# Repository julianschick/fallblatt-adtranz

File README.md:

# Adtranz-Fallblattmodule

ESP32-Mikrocontrollercode und Leiterplattenlayouts für den Betrieb von 20 Adtranz-Fallblattmodulen mit Alphanumerischer Zeichenpalette.

## Funktionsweise

Wie in [diesem Mikrocontroller.net-Thread](https://www.mikrocontroller.net/topic/460531) auch gut mit Schaltplan erläutert, sind die Fallblattmodule mit einer absoluten Positionierung anhand einer 6-Bit-Gray-Codierungsscheibe versehen. 6 Infrarotdioden sind hinter einer auf der Hauptachse mitrotierenden Scheibe angebracht, deren ringförmige Aussparungen einen Gray-Code ergeben, der mit Infrarotsensoren auf der anderen Seite der Scheibe ausgelesen werden kann.

Meine Ansteuerung besteht aus einem Zentralmodul und einem Steckermodul für jedes einzelne Fallblattmodul. Das Steckermodul bzw. dessen Platine wird mit einen "Card-Edge-Connector" direkt an das Fallblattmodul angesteckt. Auf dem Steckermodul befindet sich lediglich ein Shift-Register und ein Komparatorchip. Der Motor wird, solange mit Betriebsspannung versorgt, solange weiterdrehen, bis der im Shift-Register eingestellte Code auf der Codierungsscheibe erreicht ist.

Auf dem Zentralmodul sitzt ein ESP32, der die als Daisy-Chain verbundenen Steckermodule bzw. deren Shift-Register als ein langes Shift-Register befüllt. Da die Steuerleitungen dieser Shift-Registerkette durchaus lang sind (ca. 2m) ist es erforderlich diese direkt am Ausgang 
des Mikrocontrollers seriell zu terminieren, da die saubere Signalübertragung durch Spiegelungseffekte andernfalls nicht mehr gewährleistet ist.

<div align="center">

</div>

Außerdem war [weitere Stabilisierung nötig](https://www.mikrocontroller.net/topic/573166) bei den Schaltvorgängen des Motor-Relais im Fallblattmoduls. Direkt an den Motor wurde ein 100nF-Entstörkondensator 'angefrankensteint'. Außerdem ist ein 10 Ohm/2,2uF Snubberglied über den Relaiskontakt (zwischen 24 VAC N auf der Steckermodulplatine und 'b' auf der Platine des Fallblattmoduls gelegt) um für Ruhe beim Schalten zu sorgen. Ohne diese Maßnahmen hat die Abschaltung des Motors bei erreichen der gewünschten Stellung der Hauptachse nicht gut funktioniert.

## Leiterplattenlayouts

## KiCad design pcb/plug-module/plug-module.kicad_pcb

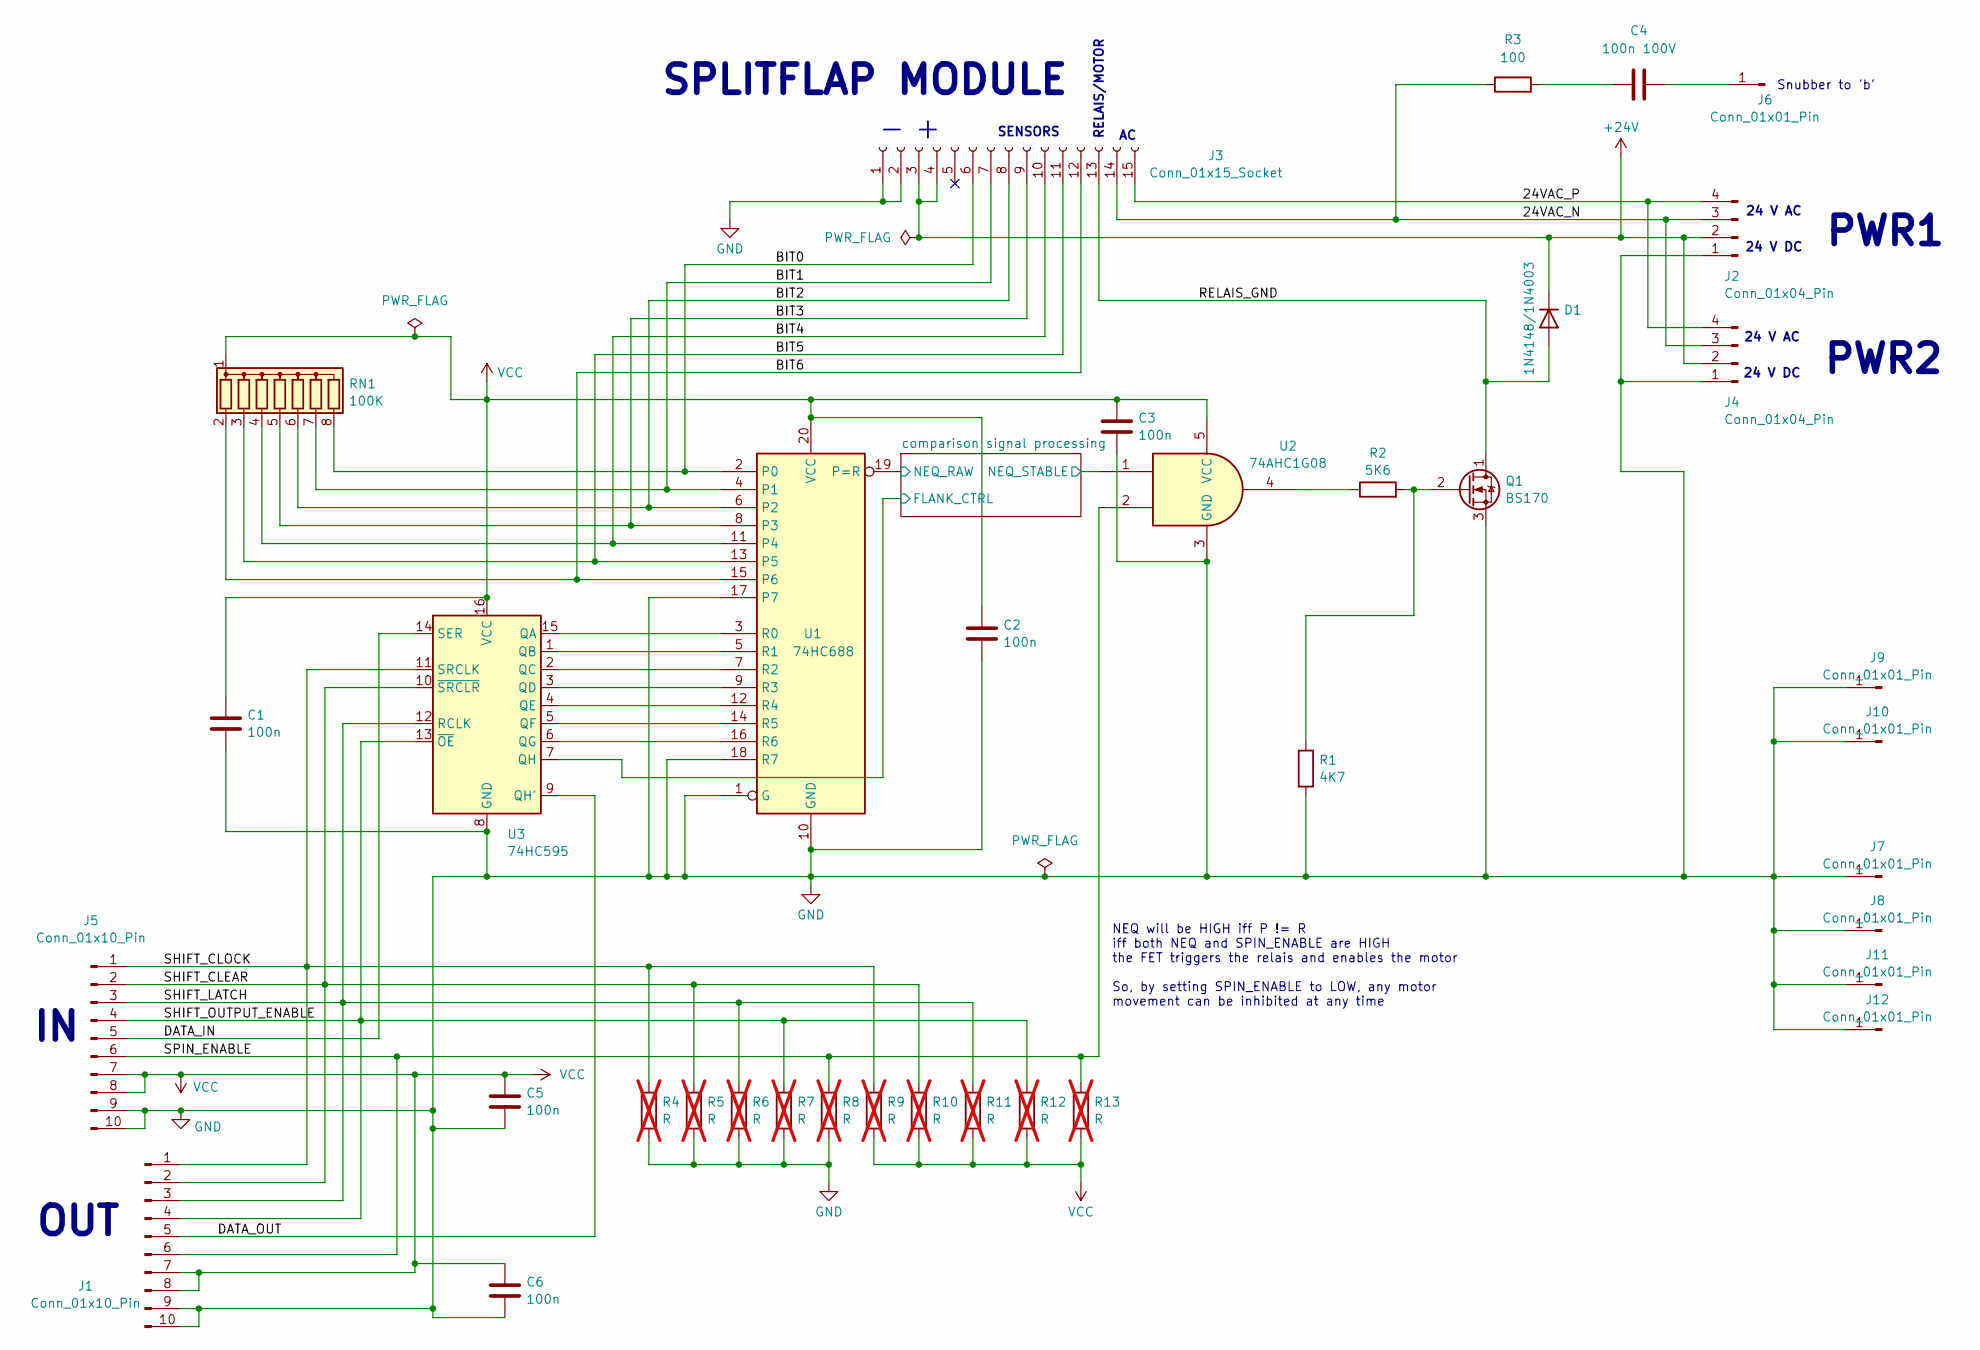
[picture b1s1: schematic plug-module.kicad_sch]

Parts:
C1, C2, C3, C5, C6: 100n; C_Disc_D4.3mm_W1.9mm_P5.00mm
C4: 100n 100V; C_Rect_L9.0mm_W3.6mm_P7.50mm_MKT
D1: 1N4148/1N4003; D_T-1_P10.16mm_Horizontal
J1, J5: Conn_01x10_Pin; TE_CON_5499922-1_BIGGERHULL
J2, J4: Conn_01x04_Pin; JST_VH_B4PS-VH_1x04_P3.96mm_Horizontal
J3: Conn_01x15_Socket; 1x15_CardEdge
J6: Conn_01x01_Pin; PinHeader_1x01_P2.54mm_Horizontal
J7, J8, J11, J12: Conn_01x01_Pin; TestPoint_Pad_4.0x4.0mm
J9, J10: Conn_01x01_Pin; Langloch-Pad
Q1: BS170; TO-92_Inline
R1: 4K7; R_Axial_DIN0207_L6.3mm_D2.5mm_P10.16mm_Horizontal
R2: 5K6; R_Axial_DIN0207_L6.3mm_D2.5mm_P10.16mm_Horizontal
R3: 100; R_Axial_DIN0207_L6.3mm_D2.5mm_P10.16mm_Horizontal
R4, R5, R6, R7, R8, R9, R10, R11, R12, R13: R; R_1206_3216Metric_Pad1.30x1.75mm_HandSolder; not fitted
RN1: 100K; R_Array_SIP8
U1: 74HC688; DIP-20_W7.62mm
U2: 74AHC1G08; TSSOP-5_Handsoldering
U3: 74HC595; DIP-16_W7.62mm

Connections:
+24V: D1.1 (K), J2.2, J3.3, J3.4, J4.2
/24VAC_N: J2.3, J3.14, J4.3, R3.1
/24VAC_P: J2.4, J3.15, J4.4
/BIT0: J3.6, RN1.8 (R7), U1.2 (P0)
/BIT1: J3.7, RN1.7 (R6), U1.4 (P1)
/BIT2: J3.8, RN1.6 (R5), U1.6 (P2)
/BIT3: J3.9, RN1.5 (R4), U1.8 (P3)
/BIT4: J3.10, RN1.4 (R3), U1.11 (P4)
/BIT5: J3.11, RN1.3 (R2), U1.13 (P5)
/BIT6: J3.12, RN1.2 (R1), U1.15 (P6)
/DATA_IN: J5.5, U3.14 (SER)
/DATA_OUT: J1.5, U3.9 (QH')
/RELAIS_GND: D1.2 (A), J3.13, Q1.1 (D)
/SHIFT_CLEAR: J1.2, J5.2, R5.1, R10.1, U3.10 (~SRCLR)
/SHIFT_CLOCK: J1.1, J5.1, R4.1, R9.1, U3.11 (SRCLK)
/SHIFT_LATCH: J1.3, J5.3, R6.1, R11.1, U3.12 (RCLK)
/SHIFT_OUTPUT_ENABLE: J1.4, J5.4, R7.1, R12.1, U3.13 (~OE)
/SPIN_ENABLE: J1.6, J5.6, R8.1, R13.1, U2.2
/comparison signal processing/FLANK_CTRL: U3.7 (QH); also elsewhere on the board
/comparison signal processing/NEQ_RAW: U1.19 (P=R); also elsewhere on the board
/comparison signal processing/NEQ_STABLE: U2.1; also elsewhere on the board
GND: C1.2, C2.2, C3.2, C5.2, C6.2, J1.9, J1.10, J2.1, J3.1, J3.2, J4.1, J5.9, J5.10, J7.1 (Pin_1_1), J8.1 (Pin_1_1), J9.1 (Pin_1_1), J10.1 (Pin_1_1), J11.1 (Pin_1_1), J12.1 (Pin_1_1), Q1.3 (S), R1.2, R4.2, R5.2, R6.2, R7.2, R8.2, U1.1 (G), U1.10 (GND), U1.17 (P7), U1.18 (R7), U2.3 (GND), U3.8 (GND); also elsewhere on the board
unnamed: C4.1, R3.2
unnamed: C4.2, J6.1 (Pin_1_1)
unnamed: Q1.2 (G), R1.1, R2.2
unnamed: R2.1, U2.4
unnamed: U1.3 (R0), U3.15 (QA)
unnamed: U1.5 (R1), U3.1 (QB)
unnamed: U1.7 (R2), U3.2 (QC)
unnamed: U1.9 (R3), U3.3 (QD)
unnamed: U1.12 (R4), U3.4 (QE)
unnamed: U1.14 (R5), U3.5 (QF)
unnamed: U1.16 (R6), U3.6 (QG)
VCC: C1.1, C2.1, C3.1, C5.1, C6.1, J1.7, J1.8, J5.7, J5.8, R9.2, R10.2, R11.2, R12.2, R13.2, RN1.1 (common), U1.20 (VCC), U2.5 (VCC), U3.16 (VCC); also elsewhere on the board

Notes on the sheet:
NEQ will be HIGH iff P != R iff both NEQ and SPIN_ENABLE are HIGH the FET triggers the relais and enables the motor So, by setting SPIN_ENABLE to LOW, any motor movement can be inhibited at any time
PWR2
PWR1
SENSORS
Snubber to 'b'
OUT
24 V DC
24 V AC
RELAIS/MOTOR
SPLITFLAP MODULE

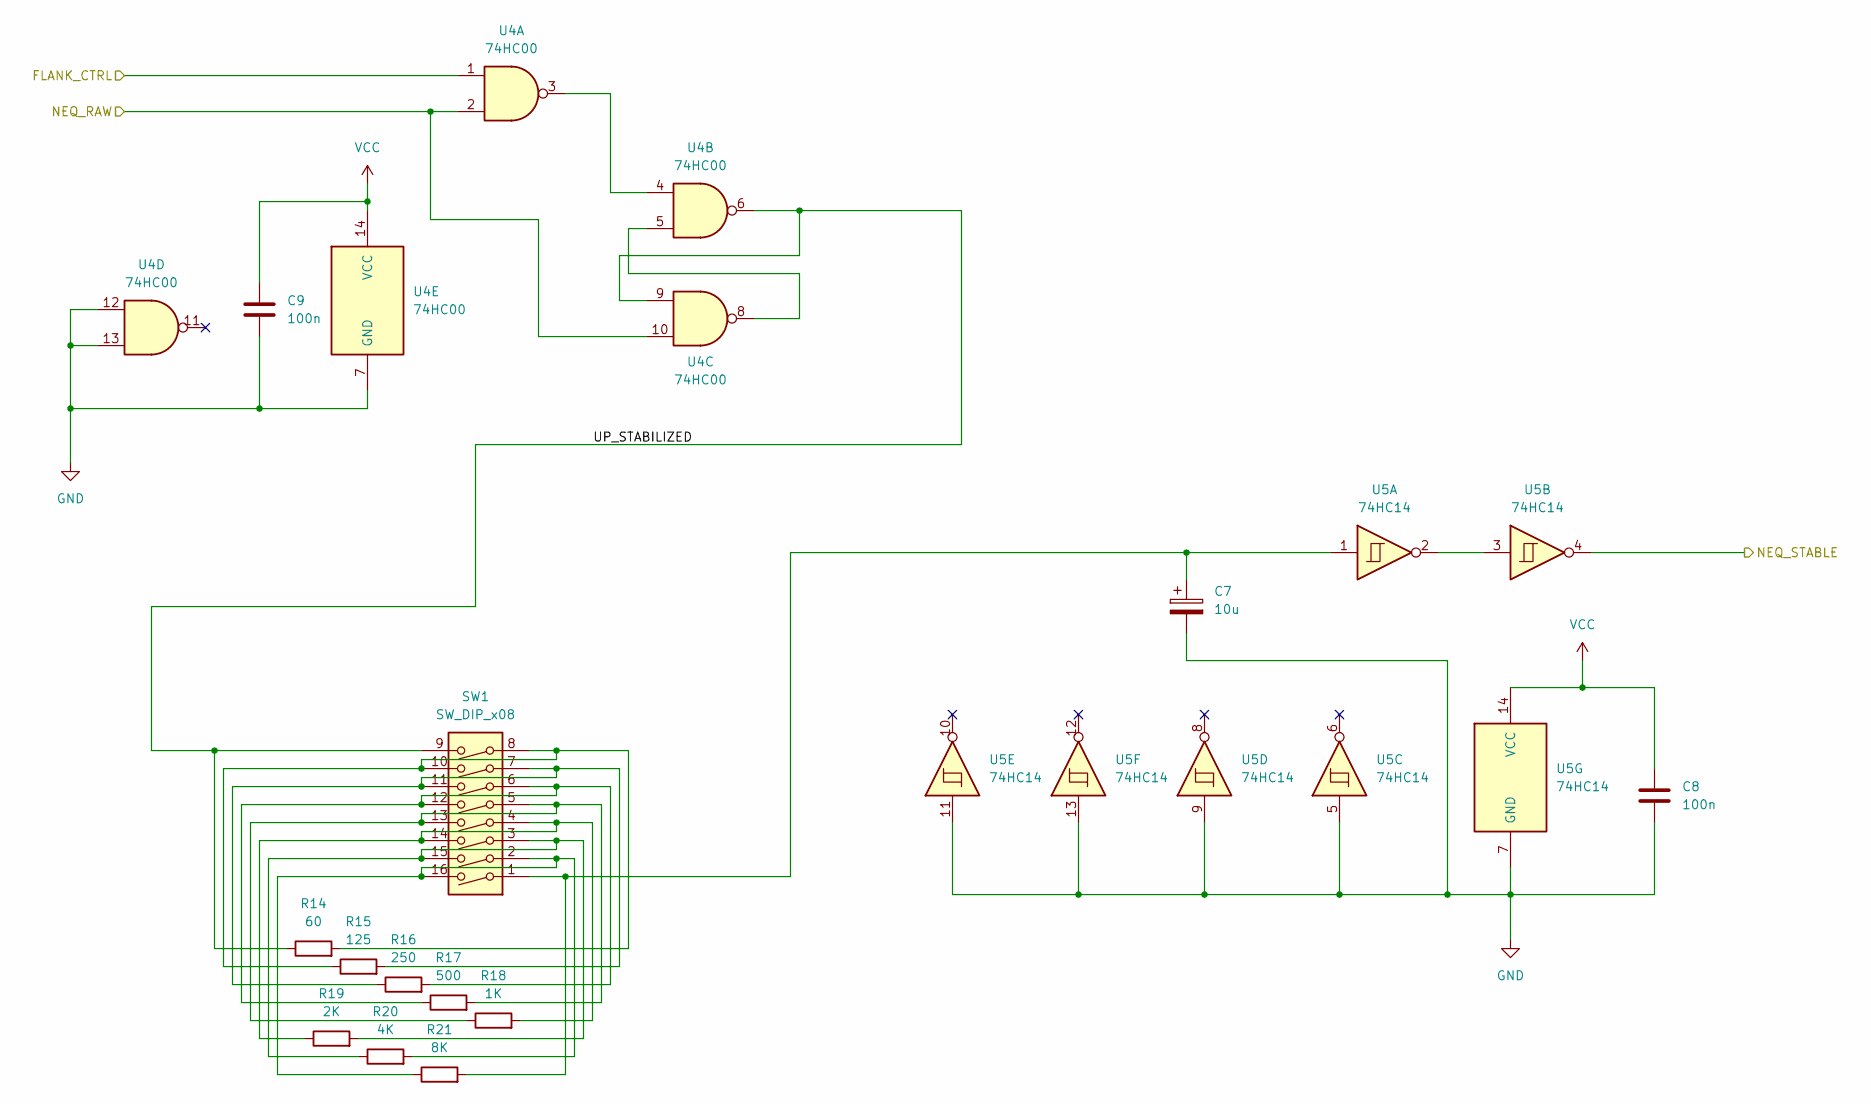
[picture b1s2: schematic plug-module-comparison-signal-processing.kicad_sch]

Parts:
C7: 10u; CP_Radial_D5.0mm_P2.00mm
C8, C9: 100n; C_Disc_D4.3mm_W1.9mm_P5.00mm
R14: 60; R_Axial_DIN0207_L6.3mm_D2.5mm_P10.16mm_Horizontal
R15: 125; R_Axial_DIN0207_L6.3mm_D2.5mm_P10.16mm_Horizontal
R16: 250; R_Axial_DIN0207_L6.3mm_D2.5mm_P10.16mm_Horizontal
R17: 500; R_Axial_DIN0207_L6.3mm_D2.5mm_P10.16mm_Horizontal
R18: 1K; R_Axial_DIN0207_L6.3mm_D2.5mm_P10.16mm_Horizontal
R19: 2K; R_Axial_DIN0207_L6.3mm_D2.5mm_P10.16mm_Horizontal
R20: 4K; R_Axial_DIN0207_L6.3mm_D2.5mm_P10.16mm_Horizontal
R21: 8K; R_Axial_DIN0207_L6.3mm_D2.5mm_P10.16mm_Horizontal
SW1: SW_DIP_x08; DIP-16_W7.62mm
U4: 74HC00; DIP-14_W7.62mm
U5: 74HC14; DIP-14_W7.62mm

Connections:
/comparison signal processing/FLANK_CTRL: U4.1; also elsewhere on the board
/comparison signal processing/NEQ_RAW: U4.2, U4.10; also elsewhere on the board
/comparison signal processing/NEQ_STABLE: U5.4; also elsewhere on the board
/comparison signal processing/UP_STABILIZED: R14.1, SW1.9, U4.6, U4.9
GND: C7.2, C8.2, C9.2, U4.7 (GND), U4.12, U4.13, U5.5, U5.7 (GND), U5.9, U5.11, U5.13; also elsewhere on the board
unnamed: C7.1, R21.2, SW1.1, U5.1
unnamed: R14.2, R15.1, SW1.8, SW1.10
unnamed: R15.2, R16.1, SW1.7, SW1.11
unnamed: R16.2, R17.1, SW1.6, SW1.12
unnamed: R17.2, R18.1, SW1.5, SW1.13
unnamed: R18.2, R19.1, SW1.4, SW1.14
unnamed: R19.2, R20.1, SW1.3, SW1.15
unnamed: R20.2, R21.1, SW1.2, SW1.16
unnamed: U4.3, U4.4
unnamed: U4.5, U4.8
unnamed: U5.2, U5.3
VCC: C8.1, C9.1, U4.14 (VCC), U5.14 (VCC); also elsewhere on the board

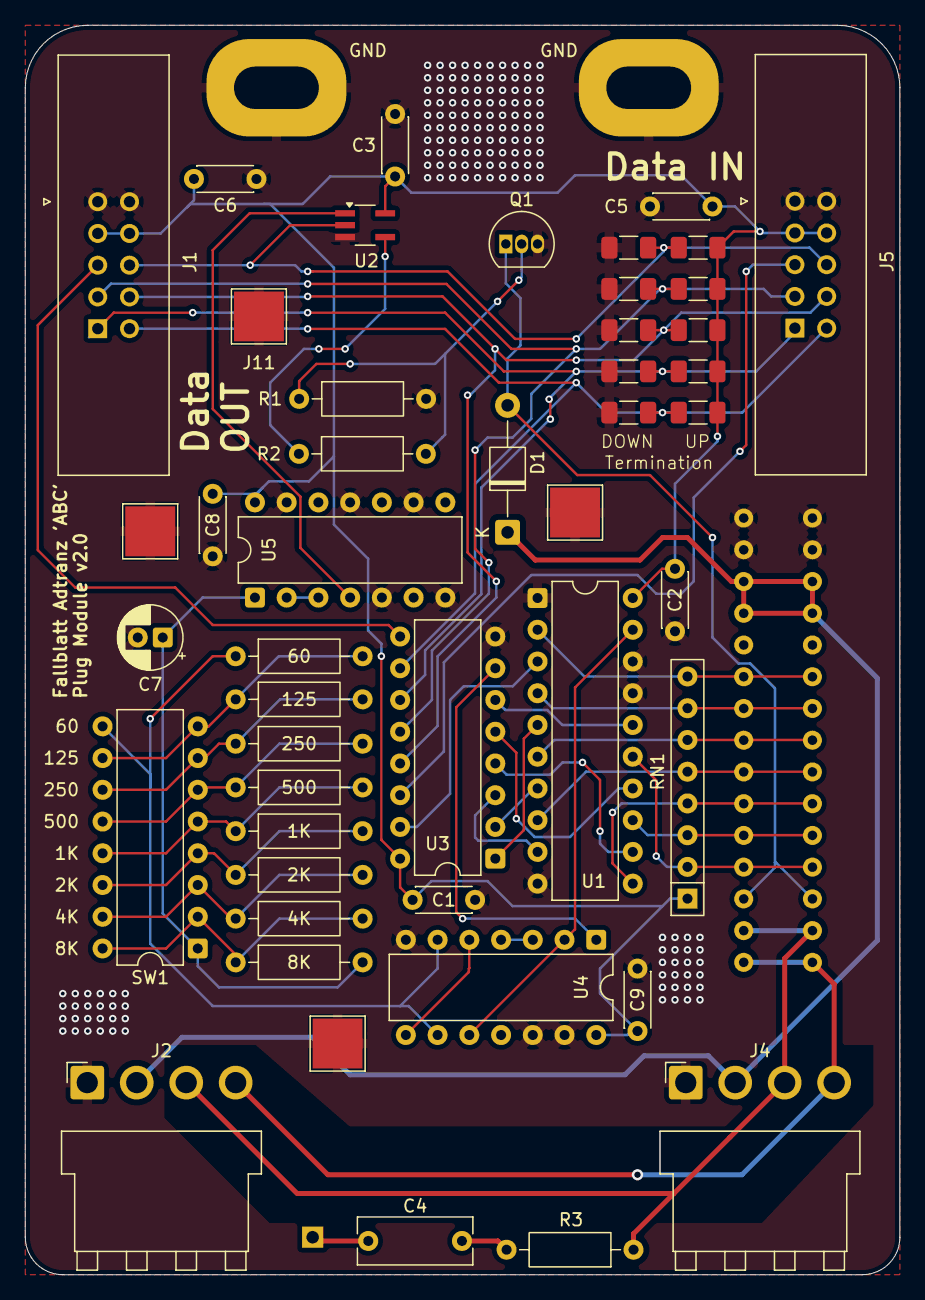
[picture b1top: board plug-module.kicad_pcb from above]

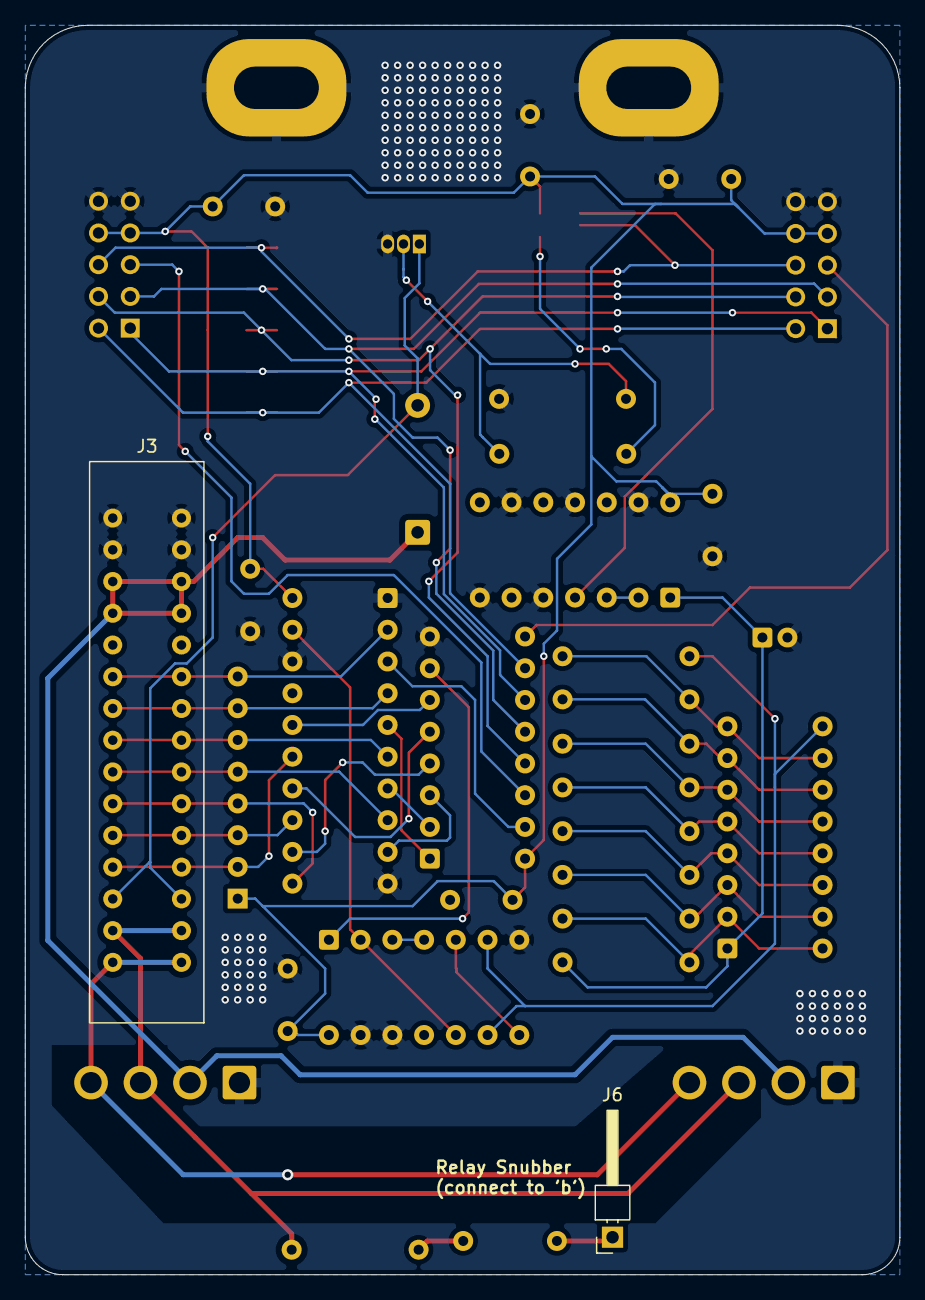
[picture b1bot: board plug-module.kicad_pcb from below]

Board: 2 copper layers, 70.0 x 100.0 mm, 51 parts (2 on the bottom side), 46 nets.

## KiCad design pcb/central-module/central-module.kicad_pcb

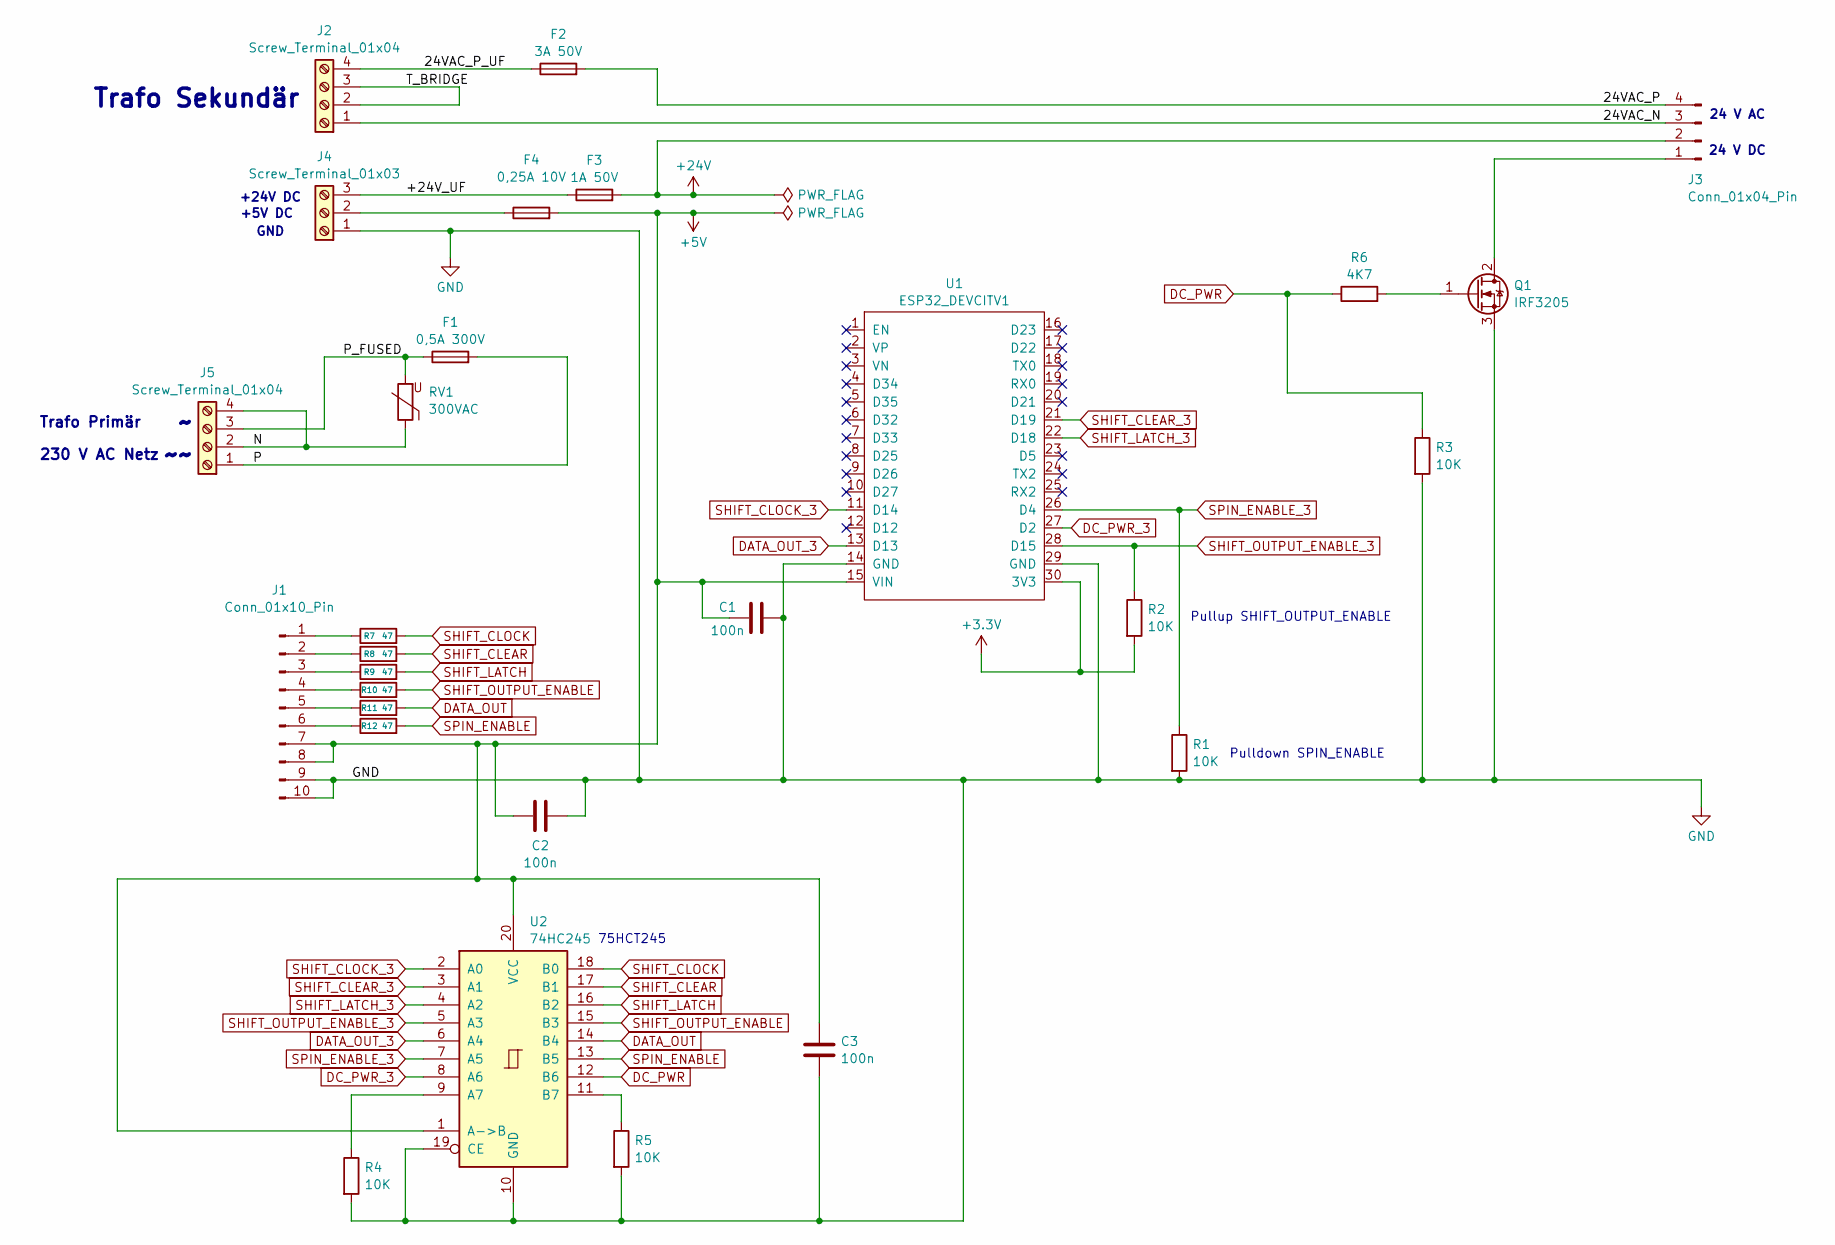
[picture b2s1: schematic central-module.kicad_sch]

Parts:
C1, C2, C3: 100n; C_Disc_D4.3mm_W1.9mm_P5.00mm
F1: 0,5A 300V; Fuseholder_Schurter_OGN_22.5
F2: 3A 50V; Fuseholder_Schurter_OGN_22.5
F3: 1A 50V; Fuseholder_Schurter_OGN_22.5
F4: 0,25A 10V; Fuseholder_Schurter_OGN_22.5
J1: Conn_01x10_Pin; TE_CON_5499922-1_BIGGERHULL
J2, J5: Screw_Terminal_01x04; TerminalBlock_MetzConnect_Type175_RT02704HBLC_1x04_P7.50mm_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
J3: Conn_01x04_Pin; JST_VH_B4PS-VH_1x04_P3.96mm_Horizontal
J4: Screw_Terminal_01x03; TerminalBlock_MetzConnect_Type011_RT05503HBLC_1x03_P5.00mm_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
Q1: IRF3205; TO-220-3_Vertical
R1, R2, R3, R4, R5: 10K; R_Axial_DIN0207_L6.3mm_D2.5mm_P10.16mm_Horizontal
R6: 4K7; R_Axial_DIN0207_L6.3mm_D2.5mm_P10.16mm_Horizontal
R7, R8, R9, R10, R11, R12: 47; R_Axial_DIN0207_L6.3mm_D2.5mm_P10.16mm_Horizontal
RV1: 300VAC; RV_Disc_D15.5mm_W3.9mm_P7.5mm
U1: ESP32_DEVCITV1; ESP32_DEVKITV1
U2: 74HC245; DIP-20_W7.62mm

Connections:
+3.3V: R2.2, U1.30 (3V3)
+5V: C1.2, C2.2, C3.1, F4.2, J1.7, J1.8, U1.15 (VIN), U2.1 (A->B), U2.20 (VCC)
+24V: F3.2, J3.2
/24VAC_N: J2.1, J3.3
/24VAC_P: F2.2, J3.4
/24VAC_P_UF: F2.1, J2.4
/+24V_UF: F3.1, J4.3
/N: J5.2, J5.4, RV1.1
/P: F1.2, J5.1
/P_FUSED: F1.1, J5.3, RV1.2
/T_BRIDGE: J2.2, J2.3
DATA_OUT: R11.2, U2.14 (B4)
DATA_OUT_3: U1.13 (D13), U2.6 (A4)
DC_PWR: R3.1, R6.1, U2.12 (B6)
DC_PWR_3: U1.27 (D2), U2.8 (A6)
GND: C1.1, C2.1, C3.2, J1.9, J1.10, J4.1, Q1.3 (S), R1.2, R3.2, R4.2, R5.2, U1.14 (GND), U1.29 (GND), U2.10 (GND), U2.19 (CE)
unnamed: J1.1, R7.1
unnamed: J1.2, R8.1
unnamed: J1.3, R9.1
unnamed: J1.4, R10.1
unnamed: J1.5, R11.1
unnamed: J1.6, R12.1
unnamed: J3.1, Q1.2 (D)
unnamed: F4.1, J4.2
unnamed: Q1.1 (G), R6.2
unnamed: R4.1, U2.9 (A7)
unnamed: R5.1, U2.11 (B7)
SHIFT_CLEAR: R8.2, U2.17 (B1)
SHIFT_CLEAR_3: U1.21 (D19), U2.3 (A1)
SHIFT_CLOCK: R7.2, U2.18 (B0)
SHIFT_CLOCK_3: U1.11 (D14), U2.2 (A0)
SHIFT_LATCH: R9.2, U2.16 (B2)
SHIFT_LATCH_3: U1.22 (D18), U2.4 (A2)
SHIFT_OUTPUT_ENABLE: R10.2, U2.15 (B3)
SHIFT_OUTPUT_ENABLE_3: R2.1, U1.28 (D15), U2.5 (A3)
SPIN_ENABLE: R12.2, U2.13 (B5)
SPIN_ENABLE_3: R1.1, U1.26 (D4), U2.7 (A5)

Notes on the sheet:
+24V DC
Pulldown SPIN_ENABLE
24 V AC
24 V DC
75HCT245
230 V AC Netz
+5V DC
Trafo Primär
Pullup SHIFT_OUTPUT_ENABLE
GND
Trafo Sekundär

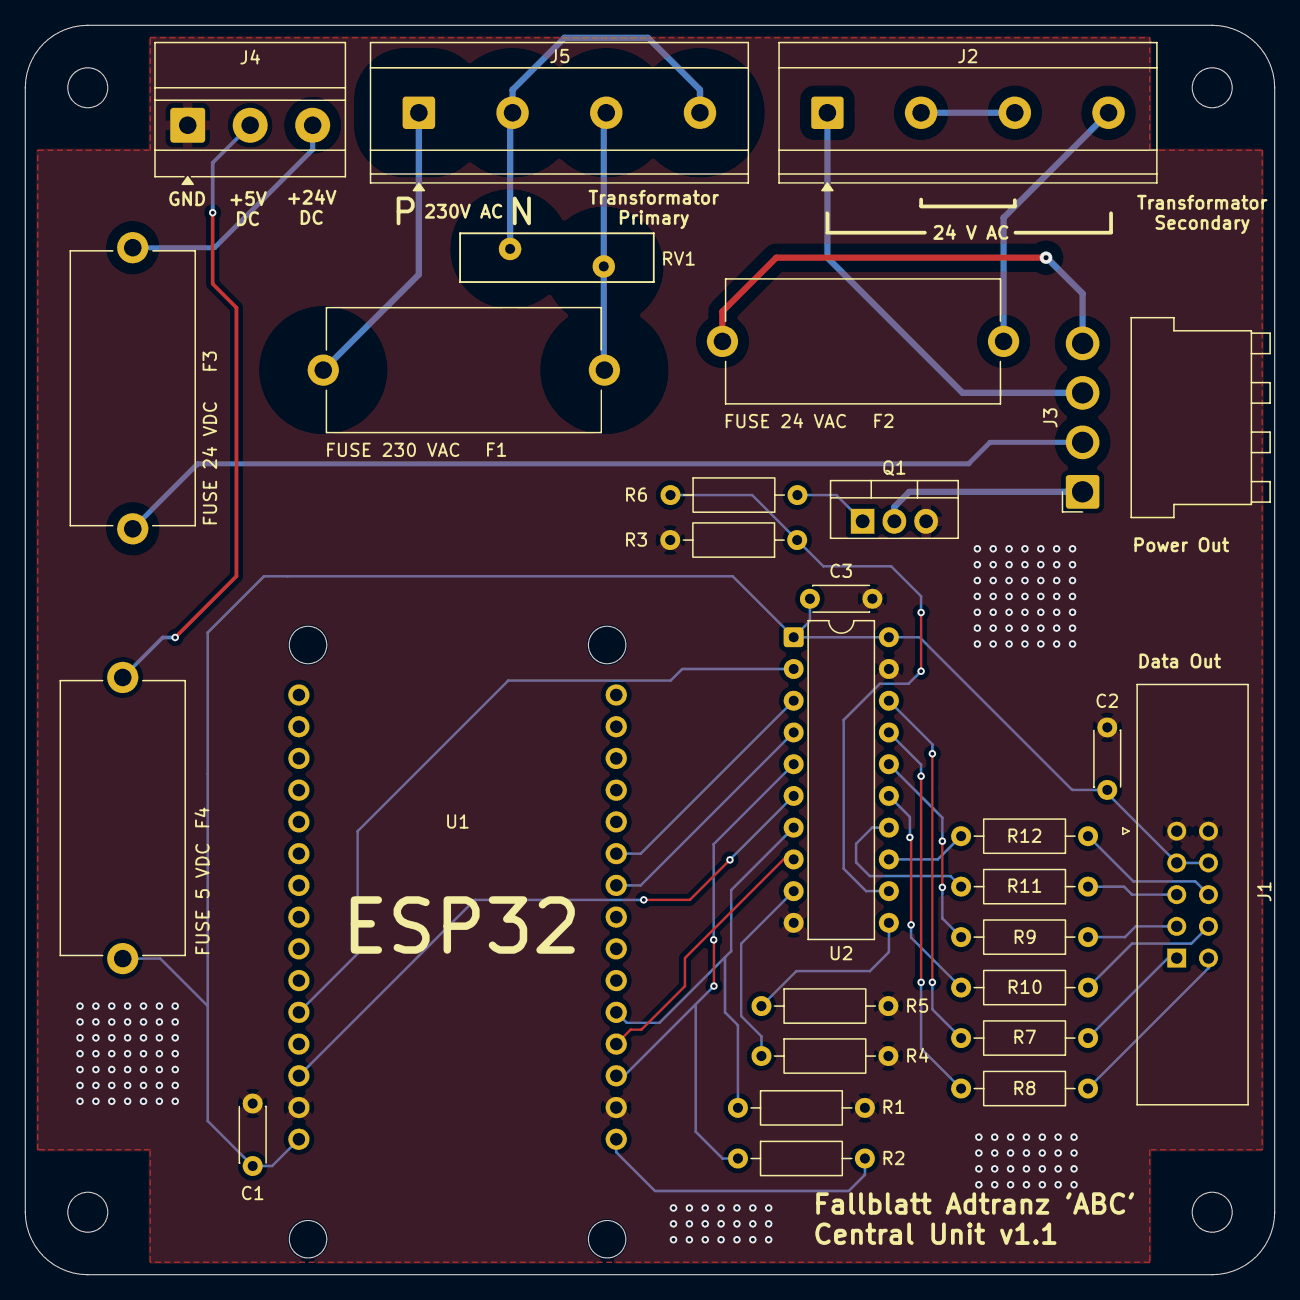
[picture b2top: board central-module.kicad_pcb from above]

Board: 2 copper layers, 100.0 x 100.0 mm, 32 parts (0 on the bottom side), 37 nets.

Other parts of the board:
L1, L2, L3, L4: MountingHole_3.2mm_M3

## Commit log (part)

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2024-10-11 checks and gerber
2024-10-11 drill files
2024-11-10 improvements first soldering
2024-11-11 plug module improvements (soldering)
2024-11-13 firmware first shot
2024-11-16 first version firmware, rounded corners
2024-11-16 gerber files in gitignore
2024-11-17 dc power fet
2024-11-17 additional info
2024-11-17 firmware for testing
2024-11-18 beschriftungen sicherungen
2024-11-22 unused pins, varistor
2024-11-24 snubber, terminal resistors
2024-11-24 pcb layout plug module
2024-11-26 many improvements
2024-11-26 graytable, both pcbs
2024-11-26 fuses
2024-11-28 plug module pp snubber
2024-11-28 add onboard circuit schematic
2024-11-29 labels, datasheet, circuit doku
2024-11-30 completed onboard circuit
2024-11-30 review
2024-12-01 esphome firmware, image moved
2024-12-05 graycode vs inverted gray
2024-12-12 init
2024-12-12 yaml secrets
2024-12-12 r net 100k
2024-12-29 python/esphome update
2025-01-01 currents / number of mods
2025-01-05 14 modules, central pcb serial termination
2025-01-05 disable dma for spi
2025-03-03 convert to kicad 9
2025-03-05 central-module.kicad_sch -> kicad 9
2025-03-15 full 20 module current measurement and fuses
2025-06-29 new terminal blocks 7.5 and schurter fuseholders
2025-07-07 project settings
2025-07-13 central module final v1.1
2025-08-25 firmware update
2025-12-05 add images
2025-12-05 add daisy-chaining image
